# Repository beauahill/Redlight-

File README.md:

# Redlight – ESP32 goal light

Firmware to bring a dead light-tower goal light (like the Bud Light Red Light)
back to life with a **Seeed XIAO ESP32-C6**. When one of your favorite NHL
teams scores, it fires the tower's lights in sequence to make the rotating
strobe and plays a horn/siren through the original speaker. It runs off a **wall power supply** instead of
batteries, and there's no phone app: everything is set up from a web page the
light serves itself.

* Polls the public NHL score feed (`api-web.nhle.com`), every 5 s during
  your teams' games and slower otherwise
* Pick any number of favorite teams
* **TV delay** setting so the light goes off when *you* see the goal, not
  30 s early
* Plays your own `horn.wav` (upload it from the browser), or a built-in
  synthesized horn + siren if none is installed
* Goals that are overturned on review are handled, and goals scored
  before power-up are ignored
* Light patterns: **Lighthouse** (default: a narrow beam sweeps around the
  tower, one bank flashing after another), **Spin** (softer, with a fading
  tail), **Chase**, **Strobe**, **Alternate**, with adjustable speed and brightness

* The housing's original buttons: TEST to test/stop (hold 10 s to reset
  WiFi), VOL+ / VOL- to change the volume

Hardware and wiring: **[docs/WIRING.md](docs/WIRING.md)**

## Flash from a browser (no install)

`firmware/redlight-xiao-c6-full-0x0.bin` is a ready-built image for the Seeed
XIAO ESP32-C6 (bootloader, partition table and firmware in one file). Each
file name ends with the flash address it must be written to.

1. Download the file, and plug the XIAO into a computer with a USB-C **data** cable.
2. In Chrome or Edge, open <https://espressif.github.io/esptool-js/>.
3. Click **Connect** and pick the XIAO's serial port ("USB JTAG/serial debug unit").
4. Set **Flash Address** to `0x0`, choose the file, and click **Program**.
5. When it finishes, unplug and replug the XIAO (or press its reset button).

**Updating a board that is already set up:** flash
`redlight-xiao-c6-update-0x10000.bin` at address **`0x10000`**
instead. That replaces only the firmware and keeps your WiFi and settings; the
full image at `0x0` erases them. An update file written to `0x0` by mistake
overwrites the bootloader ("Invalid image block, can't boot"); flash the full
image at `0x0` to recover.

If no port shows up, or the board keeps resetting, hold the XIAO's **BOOT**
button while plugging it in.
The image is rebuilt by hand, so it can lag behind the source; build with
PlatformIO (below) after changing any code.

## Build & flash

Install [PlatformIO](https://platformio.org/install) (VS Code extension or CLI), then:

```bash
pio run -e xiao_c6 -t upload     # Seeed XIAO ESP32-C6 (the board on the tower PCB)
pio run -e esp32c6 -t upload     # ESP32-C6 DevKitC-1
pio device monitor               # serial log
```

If upload won't start, hold **BOOT** while plugging in USB.

The build uses USB-CDC for `Serial` (right for XIAO boards). On a board whose
USB goes through a UART chip, remove `-D ARDUINO_USB_CDC_ON_BOOT=1` to see logs.

## First-time setup

1. Power it up. It creates a WiFi network called **`GoalLight-Setup`**.
2. Join it from your phone. A captive portal opens (if not, browse to
   `192.168.4.1`). Choose your home WiFi and enter the password.
3. It reboots and joins your network. Open **http://goallight.local**
   (or the IP printed on the serial monitor / shown in your router).
4. Tick your teams, set the TV delay, and hit **Save**. Press **Test goal**.

## The horn sound

The original sound lived on the fried board, so you'll need to supply one:
a recording of a goal horn, your team's arena horn + goal song, etc. Convert
it and upload from the web page:

```bash
./tools/make_horn.sh goal-horn.mp3          # -> horn.wav (needs ffmpeg)
```

Any **16-bit PCM WAV** (mono or stereo, any sample rate) works. The filesystem
holds about 2 MB, roughly 45 s at the script's 22 kHz mono. The horn plays once
per goal, and the lights run for the **Light duration** setting.

## Syncing to your TV

Cable/satellite is typically 5–15 s behind the live feed and streaming
30–60 s or more. Leave the delay at 0 for one game and time how long it is
from the light going off to seeing the goal on your TV. Put that number in
**TV / stream delay**.

## Project layout

```
src/config.h      pins and defaults
src/main.cpp      WiFi setup, button, main loop
src/nhl.cpp       NHL score polling + goal detection
src/tower.cpp     light sequencing / patterns (runs in its own task)
src/celebrate.cpp goal celebration, WAV player, synth siren
src/web.cpp       settings page, status, WAV upload
src/settings.cpp  settings stored in flash (NVS)
docs/WIRING.md    parts list and schematic
tools/make_horn.sh audio conversion helper
```

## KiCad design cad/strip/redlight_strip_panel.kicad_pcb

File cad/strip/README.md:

# Tower LED strips (for the v2 board)

New strips to replace the original six per tower, made as a 6-up panel that
JLCPCB fabricates and assembles. One panel is one light.

## The strip

Copies the original's outline (MEASURED): 148 mm tip to tip, 6.15 mm wide,
1.0 mm thick, with a 5.15 mm tab at each end. The bottom tab is 3.4 mm long
(1.6 mm board + 1.8 mm out the other side), the top one 2.9 mm (1.4 mm flange +
1.5 mm out), leaving 141.7 mm of body between the PCB and the core's flange.

* **LEDs:** 10 red PLCC-2 (3528), the first 7 mm from the top tip, then every
  11.6 mm, the same as the original.
* **Current:** each LED has its own 200 Ω resistor (the original had one
  20 Ω resistor for all ten in parallel). About 14 mA per LED, 140 mA per
  strip, the same as the original's 150 mA, so the firmware, driver chip and
  power budget don't change.
* **Back:** two copper rails the full length, + and −.
* **Bottom tab:** exposed pads on the LED face. They solder to the board's
  pads on the outside of each slot.

## Polarity: made for the v2 board

Seen from outside the tower, with the LEDs facing you and the bottom tab
down, **"+" is the right half of the tab** (printed beside the pads). That's
where the v2 board has its 5 V ring, and it's the reverse of the original
strips. So a fresh v2 board needs **none of the polarity rework**: no trace
cuts, and no TBD62783APG with crossed pins. Fit the stock **TBD62083APG** as
designed.

For a v3 board, set `PLUS_ON_RIGHT = False` in `make_strip.py` and rebuild.

## Building a fresh v2 board with these strips

1. Assemble the board as drawn in `cad/pcb/out/assembly_*.png`, with the
   TBD62083APG notch toward the XIAO. **Do not** do the cuts, the W1 wire or
   the chip swap from `rework.py`.
2. **Do add W2**, the wire from the XIAO's 5V to J1 5V (`cad/pcb/out/rework_tower_side.png`).
   On v2 the 5 V feed passes through strip D2's tab pad, and that joint was
   unreliable on the first build.
3. Put the six strips on the core (top tabs through the flange), lower the
   assembly onto the board with the bottom tabs in the slots, then fit the screw.
4. Solder each tab on **both** sides of the board. On the first build, three
   pads' plated holes didn't join the two sides, and solder on both sides
   gets around that.
5. Check with **Test lights only** → Chase before closing it up.

## Ordering (JLCPCB)

Files are in `fab/`, made by `python3 cad/strip/make_strip.py`.

**PCB**: upload `redlight-strip-gerbers.zip`.

| Setting | Value |
|---|---|
| Layers | 2 |
| Dimensions | 60.9 × 163 mm (read from the Gerbers) |
| Quantity | **5** panels = 30 strips: four lights plus six spares |
| Delivery format | **Panel by Customer** (the panel is already drawn: 6 strips, frame, mouse bites) |
| Thickness | **1.0 mm** (the board and flange slots are sized for 1.0 mm tabs) |
| Mask colour | white reflects the most light inside the dome; any colour works |
| Surface finish | HASL lead-free, or ENIG |

**PCB assembly**: top side, Economic, quantity 5, tooling holes "Added by
Customer" (they're in the frame). Upload `strip_bom.csv` and `strip_cpl.csv`.

* **The LED has no part number in the BOM.** In the parts-matching step,
  search JLCPCB's library for a red PLCC-2 3528 LED (or "3528 red") rated
  20 mA or more and pick an in-stock one. The pads take any 3.5 × 2.8 mm
  PLCC-2.
* The resistor is listed as C8218 (200 Ω 0603). Check that the match comes up
  as 200 Ω 0603 before ordering.
* **In the placement preview, check the LED polarity.** On every strip the
  cathode (the part's marked corner or notch) must point to the **top end**,
  away from the bottom tab's pads. If JLCPCB's model shows them reversed, rotate
  the LEDs 180° there. The pads are symmetrical, so that's the whole fix.

After delivery, snap the strips out and file or sand the mouse-bite nubs flush
on their long edges.

## Files

| File | What |
|---|---|
| `make_strip.py` | generates the panel, fills the copper, runs DRC, writes `fab/` |
| `redlight_strip_panel.kicad_pcb` | the panel (KiCad 7+) |
| `fab/redlight-strip-gerbers.zip` | PCB order |
| `fab/strip_bom.csv`, `fab/strip_cpl.csv` | assembly order |
| `preview.py` → `out/strip_preview.png` | the picture above |

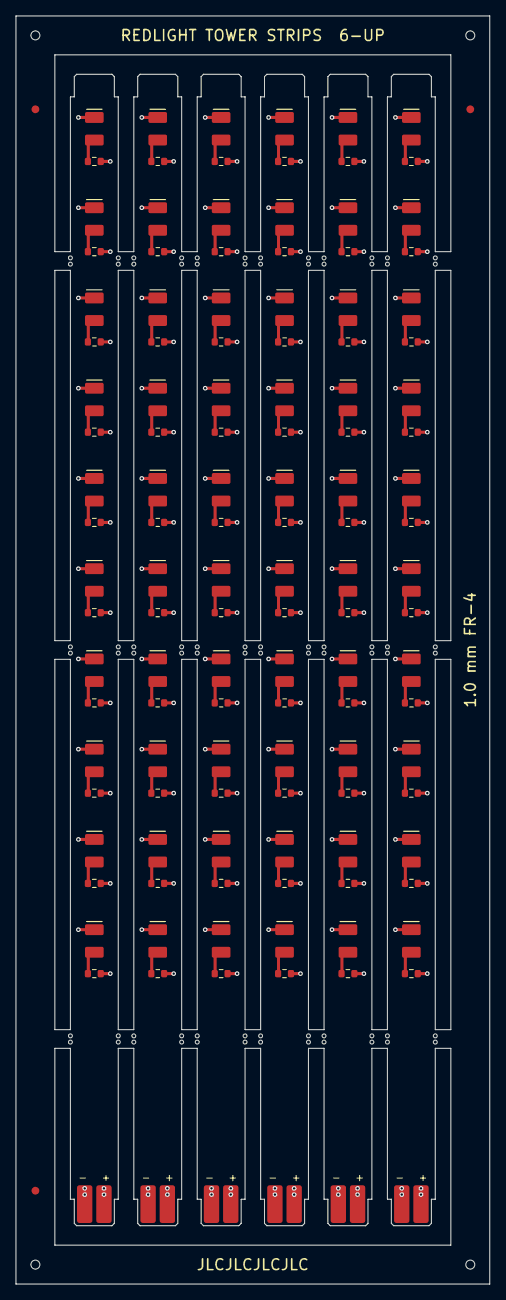
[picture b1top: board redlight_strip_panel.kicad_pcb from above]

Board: 2 copper layers, 60.9 x 163.0 mm, 169 parts (0 on the bottom side), 72 nets.

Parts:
D1, D2, D3, D4, D5, D6, D7, D8, D9, D10, D11, D12, D13, D14, D15, D16, D17, D18, D19, D20, D21, D22, D23, D24, D25, D26, D27, D28, D29, D30, D31, D32, D33, D34, D35, D36, D37, D38, D39, D40, D41, D42, D43, D44, D45, D46, D47, D48, D49, D50, D51, D52, D53, D54, D55, D56, D57, D58, D59, D60: Red 3528 LED; LED_PLCC-2_3528
FID1, FID2, FID3: Fiducial_1mm_Mask2mm
J1, J2, J3, J4, J5, J6: tab
MB1, MB2, MB3, MB4, MB5, MB6, MB7, MB8, MB9, MB10, MB11, MB12, MB13, MB14, MB15, MB16, MB17, MB18, MB19, MB20, MB21, MB22, MB23, MB24, MB25, MB26, MB27, MB28, MB29, MB30, MB31, MB32, MB33, MB34, MB35, MB36: (no value)
R1, R2, R3, R4, R5, R6, R7, R8, R9, R10, R11, R12, R13, R14, R15, R16, R17, R18, R19, R20, R21, R22, R23, R24, R25, R26, R27, R28, R29, R30, R31, R32, R33, R34, R35, R36, R37, R38, R39, R40, R41, R42, R43, R44, R45, R46, R47, R48, R49, R50, R51, R52, R53, R54, R55, R56, R57, R58, R59, R60: 200; R_0603_1608Metric
TH1, TH2, TH3, TH4: (no value)

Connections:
/S1+: J1.+, R1.2, R2.2, R3.2, R4.2, R5.2, R6.2, R7.2, R8.2, R9.2, R10.2
/S1-: D1.1, D2.1, D3.1, D4.1, D5.1, D6.1, D7.1, D8.1, D9.1, D10.1, J1.-
/S1_A1: D1.2, R1.1
/S1_A2: D2.2, R2.1
/S1_A3: D3.2, R3.1
/S1_A4: D4.2, R4.1
/S1_A5: D5.2, R5.1
/S1_A6: D6.2, R6.1
/S1_A7: D7.2, R7.1
/S1_A8: D8.2, R8.1
/S1_A9: D9.2, R9.1
/S1_A10: D10.2, R10.1
/S2+: J2.+, R11.2, R12.2, R13.2, R14.2, R15.2, R16.2, R17.2, R18.2, R19.2, R20.2
/S2-: D11.1, D12.1, D13.1, D14.1, D15.1, D16.1, D17.1, D18.1, D19.1, D20.1, J2.-
/S2_A1: D11.2, R11.1
/S2_A2: D12.2, R12.1
/S2_A3: D13.2, R13.1
/S2_A4: D14.2, R14.1
/S2_A5: D15.2, R15.1
/S2_A6: D16.2, R16.1
/S2_A7: D17.2, R17.1
/S2_A8: D18.2, R18.1
/S2_A9: D19.2, R19.1
/S2_A10: D20.2, R20.1
/S3+: J3.+, R21.2, R22.2, R23.2, R24.2, R25.2, R26.2, R27.2, R28.2, R29.2, R30.2
/S3-: D21.1, D22.1, D23.1, D24.1, D25.1, D26.1, D27.1, D28.1, D29.1, D30.1, J3.-
/S3_A1: D21.2, R21.1
/S3_A2: D22.2, R22.1
/S3_A3: D23.2, R23.1
/S3_A4: D24.2, R24.1
/S3_A5: D25.2, R25.1
/S3_A6: D26.2, R26.1
/S3_A7: D27.2, R27.1
/S3_A8: D28.2, R28.1
/S3_A9: D29.2, R29.1
/S3_A10: D30.2, R30.1
/S4+: J4.+, R31.2, R32.2, R33.2, R34.2, R35.2, R36.2, R37.2, R38.2, R39.2, R40.2
/S4-: D31.1, D32.1, D33.1, D34.1, D35.1, D36.1, D37.1, D38.1, D39.1, D40.1, J4.-
/S4_A1: D31.2, R31.1
/S4_A2: D32.2, R32.1
/S4_A3: D33.2, R33.1
/S4_A4: D34.2, R34.1
/S4_A5: D35.2, R35.1
/S4_A6: D36.2, R36.1
/S4_A7: D37.2, R37.1
/S4_A8: D38.2, R38.1
/S4_A9: D39.2, R39.1
/S4_A10: D40.2, R40.1
/S5+: J5.+, R41.2, R42.2, R43.2, R44.2, R45.2, R46.2, R47.2, R48.2, R49.2, R50.2
/S5-: D41.1, D42.1, D43.1, D44.1, D45.1, D46.1, D47.1, D48.1, D49.1, D50.1, J5.-
/S5_A1: D41.2, R41.1
/S5_A2: D42.2, R42.1
/S5_A3: D43.2, R43.1
/S5_A4: D44.2, R44.1
/S5_A5: D45.2, R45.1
/S5_A6: D46.2, R46.1
/S5_A7: D47.2, R47.1
/S5_A8: D48.2, R48.1
/S5_A9: D49.2, R49.1
/S5_A10: D50.2, R50.1
/S6+: J6.+, R51.2, R52.2, R53.2, R54.2, R55.2, R56.2, R57.2, R58.2, R59.2, R60.2
/S6-: D51.1, D52.1, D53.1, D54.1, D55.1, D56.1, D57.1, D58.1, D59.1, D60.1, J6.-
/S6_A1: D51.2, R51.1
/S6_A2: D52.2, R52.1
/S6_A3: D53.2, R53.1
/S6_A4: D54.2, R54.1
/S6_A5: D55.2, R55.1
/S6_A6: D56.2, R56.1
/S6_A7: D57.2, R57.1
/S6_A8: D58.2, R58.1
/S6_A9: D59.2, R59.1
/S6_A10: D60.2, R60.1

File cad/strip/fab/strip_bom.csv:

Comment,Designator,Footprint,LCSC Part #
"Red LED, PLCC-2 3528, 620-630 nm, 20 mA","D1,D2,D3,D4,D5,D6,D7,D8,D9,D10,D11,D12,D13,D14,D15,D16,D17,D18,D19,D20,D21,D22,D23,D24,D25,D26,D27,D28,D29,D30,D31,D32,D33,D34,D35,D36,D37,D38,D39,D40,D41,D42,D43,D44,D45,D46,D47,D48,D49,D50,D51,D52,D53,D54,D55,D56,D57,D58,D59,D60",PLCC-2 3528,
200 ohm 1% 0603,"R1,R2,R3,R4,R5,R6,R7,R8,R9,R10,R11,R12,R13,R14,R15,R16,R17,R18,R19,R20,R21,R22,R23,R24,R25,R26,R27,R28,R29,R30,R31,R32,R33,R34,R35,R36,R37,R38,R39,R40,R41,R42,R43,R44,R45,R46,R47,R48,R49,R50,R51,R52,R53,R54,R55,R56,R57,R58,R59,R60",0603,C8218

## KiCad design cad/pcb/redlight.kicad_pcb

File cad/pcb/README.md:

# Replacement tower PCB (v3)

Drop-in replacement for the original "Red Light 2.0" board: same outline
(109.5 mm circle, 74.15 mm across the flats), a 4.2 mm tower screw hole, and
six slots for the 5.15 mm LED strip tabs.

The speaker sits only 11 mm below the board, so all tall parts go on the
**tower side**, which is hidden inside the housing. On that side the red glass
necks down to ~82 mm inside diameter 13 mm above the board, so anything
outside r = 41 mm is kept under 12 mm (`fit_stl.py` checks this). The tallest
part is the XIAO at ~9.5 mm. The speaker side carries
only the angled TEST switch (~4 mm) and solder pads for wires.

## Revisions

**v3 (current files, not yet fabricated).** `redlight.kicad_pcb` and
`redlight-gerbers.zip` are v3. Changes from v2:

* **Strip polarity fixed.** +5V is on the clockwise half of each tab seen from
  the tower side (the left half, seen from outside the tower), where the strips'
  printed "+" is. The board's printed "+" marks it.
* **5 V no longer runs through a tab pad.** Every 5 V connection is laid out by
  hand in `make_pcb.py`: the tower's ring is fed from the XIAO and from
  J1/C1/C2 by its own tracks.
* **Sturdier tab pads.** 1.8 mm deep with a 0.8 mm plated hole (was 1.6 / 0.5),
  and each "+" pad reaches the ring on both layers through a second via.
* Strip numbers D1–D6 are printed beside their jumpers, and the tower side says
  "SWITCHES ON OTHER SIDE".

Checked: KiCad DRC reports 0 unconnected and 0 errors, and a separate script
check confirms the polarity, that every net is joined by copper, and that the
5 V net stays connected with the six tab pads ignored. Parts, placement and the
firmware pin map are unchanged, so the BOM and assembly drawings below apply.
The fit model in `out/` was not regenerated; the outline, slots and part
positions are the same apart from the jumpers moving out 0.2 mm.

**v2 (the board that was built).** Kept in `v2/redlight_v2.kicad_pcb`. Two faults:

* **The strip-tab pads are swapped.** +5V is on the counter-clockwise half, so
  strips soldered in as-is are reverse-biased and never light. Turning the
  strips end for end does not help: the top "+" pad is the same point as the
  bottom "+", but the pad beside it is not a return path.
* **The 5 V feed runs through strip D2's tab pad**, whose small plated hole made
  a high-resistance joint (5 V at the XIAO, 1.8–4.7 V at J1).

A built v2 board is fixed by the rework drawn by `rework.py`: three trace cuts
make the tower's common pads ground, a wire feeds 5 V straight from the XIAO to
J1, and a TBD62783APG source driver with pins 9 and 10 crossed over replaces the
TBD62083APG. Firmware is unchanged. On the first build, strips D1, D2 and D5
also needed a wire from their "−" half to a neighbour's.

## Assembly drawings

Where every part goes, with orientation notes and a soldering order:

## Files

| File | What |
|---|---|
| `redlight-gerbers.zip` | upload this to JLCPCB / PCBWay / OSH Park |
| `redlight.kicad_pcb` | KiCad board (opens in KiCad 7, 8, 9) |
| `out/redlight_fit.stl` | printable fit model (tower-side parts as blocks of real size/height) |
| `make_pcb.py` | generates the board: outline, slots, placement, nets |
| `route.py` | autoroutes (Freerouting), pours ground, DRC, Gerbers |
| `fit_stl.py` | builds the fit model from the board |
| `assembly.py` | draws the assembly drawings from the board file (no KiCad needed) |
| `rework.py` | draws the rework for built v2 boards (see Revisions) |
| `v2/redlight_v2.kicad_pcb` | the v2 board as fabricated, for reference |

There's no schematic sheet. The netlist is defined in `make_pcb.py`, and
`docs/WIRING.md` has the circuit.

## Ordering

JLCPCB settings that were checked for this board: FR-4, 2 layers, 1.6 mm,
1 oz, HASL, tented vias, 0.3 mm min via, ±0.2 mm outline tolerance, single
PCB, no assembly. Color is free choice. The six tab slots are 5.7 × 1.25 mm;
the extra length covers the router's rounded slot ends.

2 layers, 1.6 mm, any color, HASL (lead-free is fine), 1 oz copper.
The six tab slots and the screw hole are cut from the Edge.Cuts outline
(non-plated), which every fab handles at no extra cost. Leave other options
at their defaults.

## Parts (BOM)

| Ref | Part | Notes |
|---|---|---|
| U1 | Seeed XIAO ESP32-C6 | on 2× 1x7 **low-profile** female headers (≤ 5 mm), or soldered straight onto male pins. Standard 8.5 mm sockets are too tall for the glass |
| U2 | TBD62083APG | DIP-18, in a DIP-18 socket. ULN2803A also fits (dimmer) |
| R1–R6 | wire jumpers (0 Ω) | each strip has its own 20 Ω resistor ("200"). Use a clipped lead; the pads take a 1/4 W axial resistor if you ever want to dim a strip |
| R7, R8 | 100 kΩ 1/4 W axial | battery gauge divider |
| C1 | 220 µF 10 V electrolytic, 6.3 mm dia, 2.5 mm pitch, up to 6.3 × 11 mm | e.g. Rubycon 10YXS220MEFC6.3X11 (Digi-Key 1189-10YXS220MEFC6.3X11-ND). Sits inside the glass neck, so 12.5 mm tall is fine. Watch polarity |
| C2 | 100 nF (0.1 µF) ceramic, 50 V, 5.08 mm pitch | e.g. KEMET C322C104K5R5TA. The C320C104K5R5TA (Digi-Key 399-4264-ND) also works with its 2.54 mm leads spread slightly |
| J1 | solder pads, 3-way (speaker side) | 5V / GND / VBAT wires from the UPS module + cells |
| J2 | solder pads, 2-way (speaker side) | optional external TEST button |
| J3 | (holes only) | MAX98357A breakout soldered straight on its 1x7 male header, components facing away |
| SW1–SW3 | PTS645 right-angle 6 mm tact switch (speaker side) | TEST, VOL+, VOL- at the housing's buttons |
| R10, R11, R12 | 10 kΩ, 2.2 kΩ, 6.8 kΩ 1/4 W axial | button resistor ladder |
| — | MAX98357A breakout (Adafruit 3006 or clone) | **leave the screw terminal off**; solder the speaker wires to its + / − pads |

## Final check (before ordering)

* Netlist dumped from the board and compared against the firmware pin map
  (`src/config.h`): every XIAO pin, lights 1-6 in order around the tower,
  I2S, button ladder, battery sense.
* XIAO ESP32-C6 D-pin to GPIO mapping and TBD62083APG pinout (pin 9 GND,
  pin 10 COMMON) confirmed against published pinouts / the Toshiba datasheet.
* DRC: no copper errors, no unconnected pads. Fit prints checked in the housing.
* Not verifiable here: the MAX98357A module's orientation on J3. J3 has the
  pin names printed beside it; line them up with the module's labels before
  soldering (mount it upside down if that's what makes them match).

## Before ordering

- [x] Flat fit print: outline, tab slots, screw hole
- [x] Fit print v3 (no support tab): outline, slots, screw hole, parts clearance
- [ ] v2 fit print: tower-side parts clear the dome, tab sits in the recess
- [x] Tab thickness 1.0 mm, width 5.15 mm; strip inside faces 13.6 mm across (slot centers at r = 7.3 mm)
- [x] "+" is the **clockwise** half of each tab from the tower side (v2 had this backwards; confirmed by lighting a strip from a bench supply)
- [x] Button positions (TEST 39.6 mm, VOL± 48 mm and 20.15 mm apart)
- [x] Strips run on 5 V (very bright on the bench supply); worst case ~160 mA each

To regenerate after a change:

```bash
python3 cad/pcb/make_pcb.py
FREEROUTING_JAR=~/freerouting-1.9.0.jar python3 cad/pcb/route.py   # needs Java (+ xvfb-run on headless Linux)
python3 cad/pcb/fit_stl.py
```

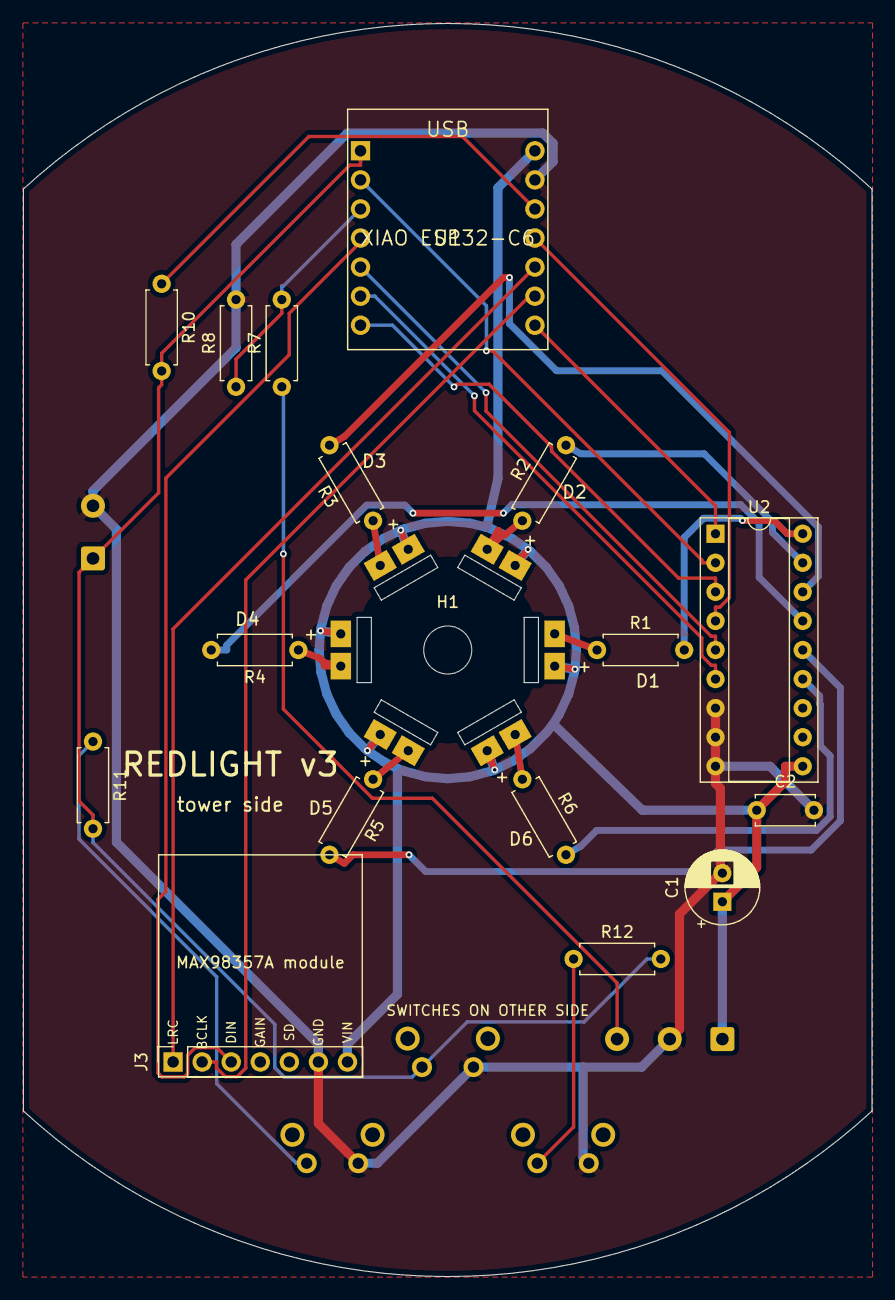
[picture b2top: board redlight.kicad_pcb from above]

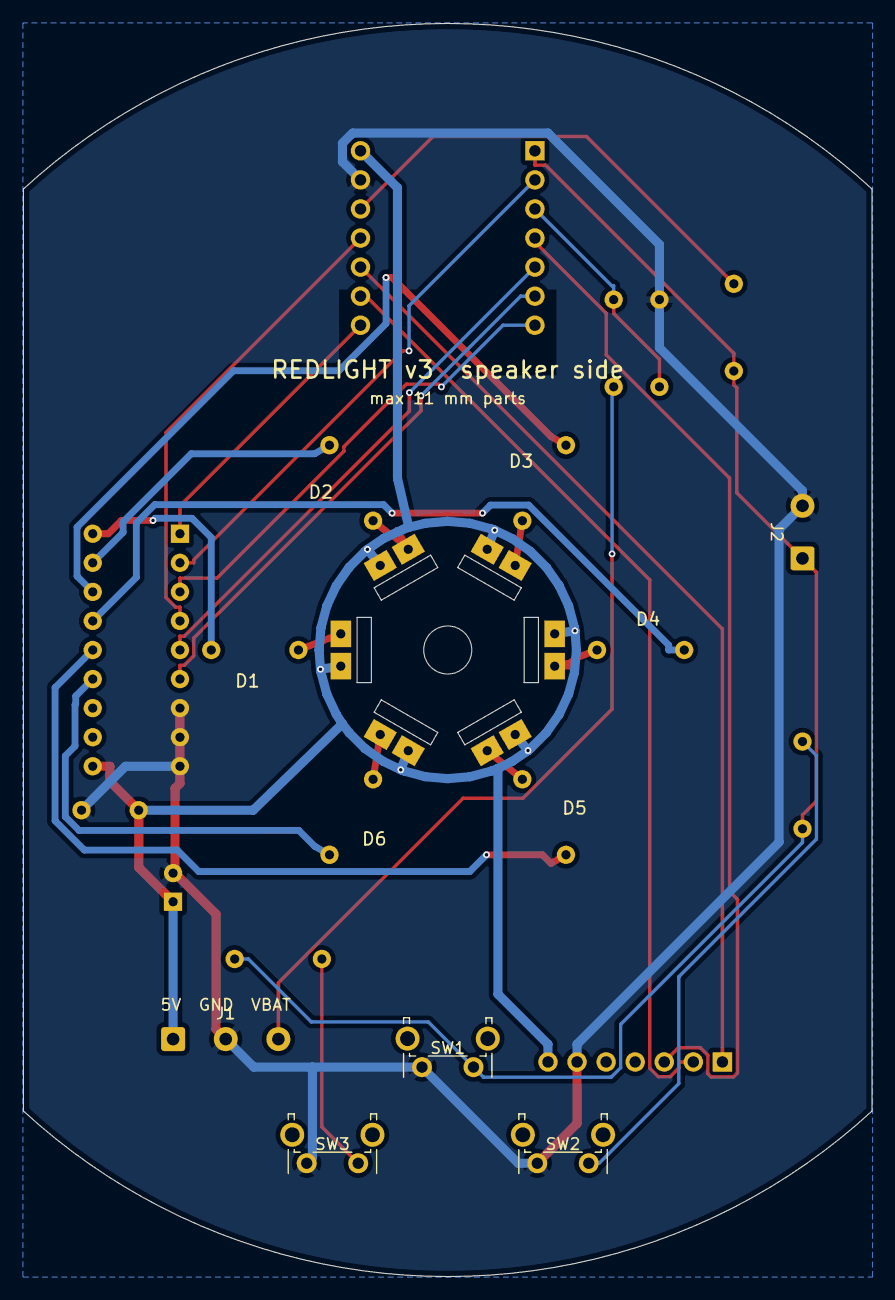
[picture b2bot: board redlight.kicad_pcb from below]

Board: 2 copper layers, 74.1 x 109.5 mm, 28 parts (5 on the bottom side), 29 nets.

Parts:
C1: 220uF 10V 6.3x7; CP_Radial_D6.3mm_P2.50mm
C2: 100nF; C_Disc_D5.0mm_W2.5mm_P5.00mm
H1: tower screw; MountingHole_3.2mm_M3
J1: 5V GND VBAT; SolderWire-0.5sqmm_1x03_P4.6mm_D0.9mm_OD2.1mm
J2: EXT TEST; SolderWire-0.5sqmm_1x02_P4.6mm_D0.9mm_OD2.1mm
J3: MAX98357A; PinSocket_1x07_P2.54mm_Vertical
LED1, LED2, LED3, LED4, LED5, LED6: strip tab
R1, R2, R3, R4, R5, R6: 0R; R_Axial_DIN0207_L6.3mm_D2.5mm_P7.62mm_Horizontal
R7, R8: 100k; R_Axial_DIN0207_L6.3mm_D2.5mm_P7.62mm_Horizontal
R10: 10k; R_Axial_DIN0207_L6.3mm_D2.5mm_P7.62mm_Horizontal
R11: 2k2; R_Axial_DIN0207_L6.3mm_D2.5mm_P7.62mm_Horizontal
R12: 6k8; R_Axial_DIN0207_L6.3mm_D2.5mm_P7.62mm_Horizontal
SW1: TEST; SW_Tactile_SPST_Angled_PTS645Vx31-2LFS
SW2: VOL+; SW_Tactile_SPST_Angled_PTS645Vx31-2LFS
SW3: VOL-; SW_Tactile_SPST_Angled_PTS645Vx31-2LFS
U1: XIAO ESP32-C6
U2: TBD62083APG; DIP-18_W7.62mm_Socket

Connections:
+3V3: R10.1, U1.3V3
+5V: C1.1, C2.1, J1.1, J3.7, LED1.+, LED2.+, LED3.+, LED4.+, LED5.+, LED6.+, U1.5V, U2.10
/BUTTONS: J2.1, R10.2, R11.2, R12.2, SW1.1, U1.D0
/I2S_BCLK: J3.2, U1.D8
/I2S_DIN: J3.3, U1.D3
/I2S_LRC: J3.1, U1.D9
/LIGHT1: U1.D7, U2.1
/LIGHT2: U1.D1, U2.2
/LIGHT3: U1.D6, U2.3
/LIGHT4: U1.D10, U2.4
/LIGHT5: U1.D4, U2.5
/LIGHT6: U1.D5, U2.6
/OUT1: R1.2, U2.18
/OUT2: R2.2, U2.17
/OUT3: R3.2, U2.16
/OUT4: R4.2, U2.15
/OUT5: R5.2, U2.14
/OUT6: R6.2, U2.13
/STRIP1-: LED1.-, R1.1
/STRIP2-: LED2.-, R2.1
/STRIP3-: LED3.-, R3.1
/STRIP4-: LED4.-, R4.1
/STRIP5-: LED5.-, R5.1
/STRIP6-: LED6.-, R6.1
/VBAT: J1.3, R7.1
/VOL+: R11.1, SW2.1
/VOL-: R12.1, SW3.1
/VSENSE: R7.2, R8.1, U1.D2
GND: C1.2, C2.2, J1.2, J2.2, J3.6, R8.2, SW1.2, SW2.2, SW3.2, U1.GND, U2.7, U2.8, U2.9
